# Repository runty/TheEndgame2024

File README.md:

# Endgame — RP2040-Zero Choc V2, nice!nano Choc V2 and nice!nano + Cirque

A 36-key [Endgame](https://github.com/OldMan6955/TheEndgame2024) repository with three builds. All three PCBs take Kailh Choc V2 (and Choc V1) hot-swap switches. Use the files for one build together; the PCBs, cases and firmware are not interchangeable.

| Build | Hardware and battery | PCB and matching case | Firmware and build notes |
| --- | --- | --- | --- |
| **RP2040-Zero Choc V2** (wired) | Waveshare RP2040-Zero, USB-C wired, original Endgame PCB outline and mounting | [JLCPCB Gerber ZIP](001%20PCB/GERBER/CHOC%20V1%20V2/TheEndgame2024_Choc_V1_V2_JLCPCB.zip) · [KiCad project](001%20PCB/KICAD/SILKSCREEN%20KICAD/) · [original case STEP](002%20CASE/TheENDGAME2024_CASE001.step) · Choc V2 plates: [3-D print](001%20PCB/PLATE%20CHOC%20V2/3D%20PRINT/), [1.2 mm FR-4/metal](001%20PCB/PLATE%20CHOC%20V2/) | [ZMK firmware](003%20FIRMWARE/zmk-endgame-rp2040-zero/) (sample keymap) · upstream [Vial UF2](003%20FIRMWARE/vial/endgame_vial.uf2) / [QMK config](003%20FIRMWARE/qmk-config-endgame/) · [Choc V1/V2 notes](docs/choc-v1-v2.md) |
| **nice!nano Choc V2** (wireless) | nice!nano v2, directly soldered 401730 LiPo (target ≤200 mAh), two axial resistors, WS2812B-V6 status LED | [223 × 96.11 mm Gerbers](001%20PCB/GERBER/NICE%20NANO%20WIRELESS/TheEndgame2024_NiceNano_223mm_THT_JLCPCB.zip) · [KiCad project](001%20PCB/KICAD/NICE%20NANO%20WIRELESS/) · [case (standard or clear LED logo) and tray](002%20CASE/NICE%20NANO%20WIRELESS/) | [ZMK firmware](003%20FIRMWARE/zmk-endgame-nice-nano/) · [build notes](docs/nice-nano-wireless.md) · [case notes](docs/nice-nano-case.md) |
| **nice!nano Choc V2 + Cirque** (wireless, touchpad) | nice!nano v2 plus a 40 mm Cirque TM040040 touchpad (curved overlay) between the thumbs; 401730 LiPo under the pad; JLCPCB-assembled SMD parts and FFC connector | [239 × 96.11 mm Gerbers + BOM/CPL](001%20PCB/GERBER/NICE%20NANO%20CIRQUE/) · [KiCad project](001%20PCB/KICAD/NICE%20NANO%20CIRQUE/) · [case, tray and pad carrier](002%20CASE/NICE%20NANO%20CIRQUE/) | [ZMK firmware](003%20FIRMWARE/zmk-endgame-nice-nano-cirque/) · [build notes](docs/nice-nano-cirque.md) |

**Case fit warning for nice!nano:** this PCB is 4 mm wider than the original and requires the matching **231 mm-wide nice!nano case** linked above. It does **not** fit the original Endgame case. Use the nice!nano-specific case files and plates.

The nice!nano version is **4 mm wider than the original PCB**. Each key half moves outward 2 mm, giving the inner keys more clearance from the controller while preserving the original outer borders. The controller, battery opening, and LED remain on the board's centreline. Its matching case retains the original height and sloped profile. The case has a relieved USB opening, and its inner thumb and top inner alpha opening edges match the original case; see the [thumb repair comparison](002%20CASE/NICE%20NANO%20WIRELESS/thumb-roof-repair-preview.png).

**Prototype status:** the RP2040-Zero Choc V2 board has been built, and all 36 keys work; keycap clearance on assembled hardware is unchecked. The nice!nano build has documented digital design, manufacturing-file, and CAD checks and has reached user assembly testing, with LED operation reported; the latest case repair, clear LED logo case, and printed thumb caps still need physical validation. Full system qualification and JLCPCB upload-preview verification remain incomplete. See the [2026-10-15 update](docs/updates-2026-10-15.md).

**nice!nano + Cirque (digital design, untested):** each half moves a further 8 mm outward (239 mm PCB, 247 mm case, same height) to fit the touchpad with its curved overlay and a 4 mm margin to the keycaps. The status LED moves to the right thumb gap. See the [nice!nano + Cirque notes](docs/nice-nano-cirque.md).

**RP2040-Zero Choc V2 PCB, top**

**nice!nano Choc V2 PCB, front**

**nice!nano Choc V2 + Cirque PCB, top**

## RP2040-Zero Choc V2 downloads

The original wired Endgame PCB with Choc V2 hot-swap support added (Choc V1 still fits). It keeps the original outline, mounting holes, controller position and 1.6 mm thickness, so it fits the original case.

| File | Download |
| --- | --- |
| JLCPCB manufacturing package | [Gerber ZIP](001%20PCB/GERBER/CHOC%20V1%20V2/TheEndgame2024_Choc_V1_V2_JLCPCB.zip) · [top](001%20PCB/GERBER/CHOC%20V1%20V2/top-preview.png) and [bottom](001%20PCB/GERBER/CHOC%20V1%20V2/bottom-preview.png) previews |
| Case | [Original case STEP](002%20CASE/TheENDGAME2024_CASE001.step) |
| Optional Choc V2 switch plates | [3-D print (recommended, test-fitted)](001%20PCB/PLATE%20CHOC%20V2/3D%20PRINT/) · [1.2 mm FR-4/metal](001%20PCB/PLATE%20CHOC%20V2/) · [notes](docs/choc-v1-v2.md#choc-v2-switch-plates) |
| Editable KiCad project | [SILKSCREEN KiCad project](001%20PCB/KICAD/SILKSCREEN%20KICAD/) (the released variant) |
| ZMK firmware (sample keymap) | [UF2](003%20FIRMWARE/zmk-endgame-rp2040-zero/firmware/endgame-rp2040-zero.uf2) · [settings reset UF2](003%20FIRMWARE/zmk-endgame-rp2040-zero/firmware/endgame-rp2040-zero-settings-reset.uf2) · [ZMK config and flashing notes](003%20FIRMWARE/zmk-endgame-rp2040-zero/) |
| Upstream QMK/Vial firmware | [Vial UF2](003%20FIRMWARE/vial/endgame_vial.uf2) · [QMK config](003%20FIRMWARE/qmk-config-endgame/); the key matrix is unchanged |
| Build details | [Compatibility, ordering, validation and prototype notes](docs/choc-v1-v2.md) |

Order **2 layers, 1.6 mm FR-4, 1 oz copper**, approximately **219 × 96.1 mm** (use the outline in the ZIP). Confirm the preview shows all 36 relief slots and 36 large centre holes. The older `SILKSCREEN GERBER` and `COPPER GERBER` folders are upstream Choc V1-only archives.

Prototype tips: the RP2040-Zero's 5V and GND pads are 0.84 mm apart, so check for a solder bridge before plugging in. If a whole column is dead, check continuity from its GP pin to the column socket tab; each column crosses to the front through a via beside its top-row switch.

## nice!nano downloads

Use the PCB, case, and firmware from this table together.

| File | Download |
| --- | --- |
| JLCPCB manufacturing package | [223 mm through-hole-resistor Gerber ZIP](001%20PCB/GERBER/NICE%20NANO%20WIRELESS/TheEndgame2024_NiceNano_223mm_THT_JLCPCB.zip) |
| Widened case (single filament) | [STL](002%20CASE/NICE%20NANO%20WIRELESS/TheENDGAME2024_NICE_NANO_CASE.stl) · [STEP](002%20CASE/NICE%20NANO%20WIRELESS/TheENDGAME2024_NICE_NANO_CASE.step) |
| Widened case with clear LED logo (two filaments) | [Bambu 3MF, two parts](002%20CASE/NICE%20NANO%20WIRELESS/LED%20LOGO/TheENDGAME2024_NICE_NANO_CASE_LED_LOGO.3mf) · body [STL](002%20CASE/NICE%20NANO%20WIRELESS/LED%20LOGO/TheENDGAME2024_NICE_NANO_CASE_LED_LOGO_BODY.stl)/[STEP](002%20CASE/NICE%20NANO%20WIRELESS/LED%20LOGO/TheENDGAME2024_NICE_NANO_CASE_LED_LOGO_BODY.step) · clear logo [STL](002%20CASE/NICE%20NANO%20WIRELESS/LED%20LOGO/TheENDGAME2024_NICE_NANO_CASE_LED_LOGO_CLEAR.stl)/[STEP](002%20CASE/NICE%20NANO%20WIRELESS/LED%20LOGO/TheENDGAME2024_NICE_NANO_CASE_LED_LOGO_CLEAR.step) · [preview](002%20CASE/NICE%20NANO%20WIRELESS/LED%20LOGO/led-logo-preview.png) · [notes](docs/nice-nano-case.md#optional-clear-led-logo-two-filament-print) |
| Removable battery tray with solder relief | [STL](002%20CASE/NICE%20NANO%20WIRELESS/TheENDGAME2024_NICE_NANO_BATTERY_TRAY.stl) · [STEP](002%20CASE/NICE%20NANO%20WIRELESS/TheENDGAME2024_NICE_NANO_BATTERY_TRAY.step) |
| Optional Choc V2 switch plates | [3-D print (recommended)](001%20PCB/PLATE%20CHOC%20V2/NICE%20NANO%20WIRELESS/3D%20PRINT/) · [1.2 mm FR-4/metal](001%20PCB/PLATE%20CHOC%20V2/NICE%20NANO%20WIRELESS/) · [notes](docs/nice-nano-case.md#choc-v2-switch-plates) |
| Editable KiCad project | [PCB](001%20PCB/KICAD/NICE%20NANO%20WIRELESS/TheEndgame2024_NiceNano.kicad_pcb) · [schematic](001%20PCB/KICAD/NICE%20NANO%20WIRELESS/TheEndgame2024_NiceNano.kicad_sch) · [project and local libraries](001%20PCB/KICAD/NICE%20NANO%20WIRELESS/) |
| nice!nano ZMK firmware (sample QWERTY keymap) | [UF2](003%20FIRMWARE/zmk-endgame-nice-nano/firmware/endgame-nice-nano-v2.uf2) · [ZMK source](003%20FIRMWARE/zmk-endgame-nice-nano/) |
| Build details | [Full BOM and assembly notes](docs/nice-nano-wireless.md) · [electrical](docs/nice-nano-electrical.md) · [case](docs/nice-nano-case.md) · [firmware](docs/nice-nano-firmware.md) |

## nice!nano JLCPCB order settings

| Setting | Value |
| --- | --- |
| Dimensions to enter | **223.00 × 96.11 mm** |
| Layers | **2** |
| Material | **FR-4** |
| Board thickness | **1.6 mm** |
| Copper weight | **1 oz** |

The measured Gerber outline is **223.000032 × 96.106067 mm**. Upload the ZIP intact: it contains the seven board layers, separate plated/non-plated drill files, and the Gerber job file. The **22 × 35 mm battery opening** is included as an internal routed contour. If dimensions need to be entered manually, use the rounded values above and check the board outline and battery opening in the preview.

## nice!nano fit and clearance

| Feature | Current design |
| --- | --- |
| Key field | 36 Choc V1/V2 hot-swap positions; each half moved outward 2 mm |
| Outer left/right 1U cap borders | **2.00 mm**, matching the original PCB with 17.5 × 16.5 mm caps |
| Keycap-to-controller clearance | **2.16 mm minimum** to the conservative 18 × 33 mm nice!nano envelope in CAD |
| Printed case width | **231 mm**, with the original overall height retained |
| USB opening | **15 mm wide**; lower side ledges removed; rear lip bevel adds 0.6 mm headroom while keeping at least 1.25 mm roof |
| Inner thumb and alpha edges | Original roof and opening edges restored beside the inner thumbs and top inner keys; existing switch plates retain 0.2 mm vertical clearance |
| Battery opening | **22 × 35 mm**, with 1 mm corner radii |
| Battery allowance checked | **18.5 × 33 × 5 mm** complete-pack envelope |

A centred **17 × 30 mm** battery leaves **2.5 mm on each side of the PCB opening**. The larger checked pack envelope leaves **1.75 mm per side and 1.0 mm at each end**, with **0.15 mm above the 5 mm-thick envelope** inside the case after the planned 0.2 mm support allowance. The actual wrapped battery and its lead exit still need measurement.

All 36 nominal **17.5 × 16.5 mm Chicago Steno 1U keycap envelopes** clear the case throughout a full-height CAD sweep, with a **0.70 mm minimum gap**, the same as the original case. Choc V2 requires **MX-stem** keycaps. The separate [thumb-cap package](006%20KEYCAPS/CHOC%20V2%20THUMBS/) includes larger-cap CAD checks; actual print tolerances and physical fit remain untested.

See the [measured layout and centreline](docs/validation/nice-nano-pcb/outer-key-symmetry.png), [keycap clearance comparison](docs/validation/nice-nano-case/cs-clearance.png), and [case preview](002%20CASE/NICE%20NANO%20WIRELESS/case-and-tray-preview.png).

The battery tray now includes an open center notch and corner relief for the underside resistor solder joints, following assembly feedback. Its screw mounts and the full planned battery support area are retained. See the [tray comparison](002%20CASE/NICE%20NANO%20WIRELESS/battery-tray-solder-clearance.png) and [case notes](docs/nice-nano-case.md).

## nice!nano electronics and assembly

- **nice!nano v2:** mount on short soldered posts, with USB facing the upper edge. Follow the [assembly-height limits](docs/nice-nano-case.md); standard sockets have not been qualified for this case.
- **Battery:** generic 401730 single-cell LiPo, target capacity ≤200 mAh. Solder its wires directly to **J1: pad 1 B+, pad 2 B−**. No JST connector is used. SW38 remains the physical battery disconnect.
- **Resistors:** R1 **330 Ω** and R2 **100 kΩ**, ordinary **¼ W axial through-hole** parts. Use nominal 6.3 × 2.5 mm bodies at **10.16 mm lead pitch**, mounted flat on the PCB's top side. The case accommodates bodies up to 6.5 × 2.5 mm; installation and lead-trimming limits are in the [BOM](docs/nice-nano-wireless.md#parts-and-assembly).
- **Status LED:** one **Worldsemi WS2812B-V6**, powered through nice!nano v2 switched VCC. With the standard case, a translucent case roof acts as the diffuser; the [clear LED logo case](docs/nice-nano-case.md#optional-clear-led-logo-two-filament-print) shows it through a transparent logo instead. The firmware adapts [zmk-rgbled-widget](https://github.com/caksoylar/zmk-rgbled-widget) for brief battery and Bluetooth/USB status flashes, then switches LED power off. See [LED meanings and limits](docs/nice-nano-firmware.md#status-indications).
- **Other parts:** C1 remains a **100 nF 0603 capacitor**, and the matrix retains **36 SOD-123 diodes and 36 Choc hot-swap sockets**. This is a hot-swap switch design; the original optional direct-solder switch pattern is not retained.

The [full parts list](docs/nice-nano-wireless.md#parts-and-assembly) includes controller posts, inserts, tray screws, feet, battery-fit assumptions, and charging requirements. Firmware is **ZMK for nice!nano v2**; the original wired QMK/Vial firmware does not apply to this revision.

## nice!nano verification

- **KiCad ERC, DRC, and schematic parity:** zero reported violations or unconnected items under the recorded rules. [ERC](docs/validation/nice-nano-schematic/erc.json) · [DRC](docs/validation/nice-nano-pcb/drc.json)
- **Independent Gerber parsing:** seven board layers, **226 plated and 148 non-plated holes/slots**, both contours closed, and drill registration checked against the PCB source. [Report](docs/validation/nice-nano-pcb/gerbers.json)
- **Mechanical checks:** mirrored key placement, preserved outer borders, centred electronics, valid single-solid STEP parts, watertight STL files, and component/keycap clearance checks. [Spacing](docs/validation/nice-nano-pcb/spacing.json) · [case](docs/validation/nice-nano-case/geometry.json)
- **Firmware:** pinned ZMK build and LED encoder host checks pass. The user reports working LED indications; hardware timing, charging, RF, and full keyboard operation remain unqualified. [Build and bring-up notes](docs/nice-nano-firmware.md)

The committed PCB is the authoritative manufacturing source. The scratch PCB generator is not a replacement for the finished routing. The [artifact manifest](docs/validation/nice-nano-artifacts.json) records source and output checksums.

## Choc V2 thumb keycaps

[Printable thumb caps and ordering notes](006%20KEYCAPS/CHOC%20V2%20THUMBS/) include **two separate connected 2 × 3 sets**: sculpted Chicago Steno thumbs and convex thumbs. Each contains **four long (1.5u) and two small (1u) caps**, with MX-style sockets for Choc V2 and removable connecting gates. These keycaps do not fit Choc V1 switches.

The cap envelopes clear the RP2040-Zero (original) and nice!nano cases in CAD. The meshes are verified locally; physical stem fit, print quality and JLC3DP acceptance remain untested. Upload the two files from the keycap folder's `upload` directory, quantity 1 each to try both profiles on one keyboard.

## Upstream documentation

This repository is based on the [original Endgame project](https://github.com/OldMan6955/TheEndgame2024). The original author's documentation is preserved below.

<details>
<summary>Original upstream README — wired Endgame, parts, credits, and photos</summary>

The following is the original project's documentation. Its controller, firmware, parts lists, manufacturing comments, and physical-test statements refer to the original Choc V1 wired design, not the RP2040-Zero Choc V2 or nice!nano Choc V2 builds above.

## Who the F... is Alice ##

Inspired by the legendary TGR Alice, the ENDGAME pays homage to a true classic. While it might not claim the top spot for ergonomics, it's design speaks for itself an iconic piece you’ll want to show off, even if it takes a bit of time for your fingers to adjust.

This low profile keyboard is built for high performance typing. Its slightly staggered layout works beautifully for both ergonomic beginners and experienced users. The unique bottomless top mount design makes it incredibly slim, lightweight, and perfect for those on the move.

## Everything You Need, All In One Place ##

Get the entire kit from KeebSupply, a trusted vendor with affordable international shipping. It’s your one stop shop for everything you need highly recommended! [Buy here](https://keeb.supply/products/endgame) 

For an excellent build guide, check out this fantastic resource from KeebSupply. I haven’t had the time to create my own guide (and honestly, I couldn’t top this one). Big thanks to @KeebSupply! [Build Guide and Supplies](https://docs.keeb.supply/endgame/) 

## PARTS LIST PCB ##

- 1x The Endgame PCB             [Gerber Files](https://github.com/OldMan6955/TheEndgame2024/tree/main/001%20PCB) 

There are now two versions of the PCB:
1.	COPPER Version:
In this version, all design elements are on the copper and mask layers. I used this version to create my prototypes. However, this version has longer loading times, and the Gerber files currently don’t work with JLCPCB. (I’d greatly appreciate any help with troubleshooting this issue.)
2.	SILKSCREEN Version:
This version is untested. All design elements have been moved to the silkscreen layer, making it much more performant on less powerful PCs. The Gerber files display correctly on JLCPCB but have not yet been tested.
Please always test the files yourself to rule out potential errors. Thank you!

- 36x Choc v1 Hotswap Sockets    [buy here](https://www.aliexpress.com/item/1005004916925259.html?) 
- 36x Diodes SOD123 / 1N4148W T4 [buy here](https://de.aliexpress.com/item/1005004309686841.html?) 
- 1x Waveshare RP2040 UGLY AF    [buy here](https://de.aliexpress.com/item/1005006354505058.html?) 

or get the better looking thingy, highly recommended

- | 01 | 0xCB Gemini             [buy here](https://keeb.supply/products/0xcb-gemini) |

## PARTS LIST FDM CASE ##

- 4x M3 6mm countersunk          [buy here](https://de.aliexpress.com/item/4001199728978.html) 
- 4x M3 5mm flathead             [buy here](https://de.aliexpress.com/item/1005005069968742.html) 

You can choose either countersunk or flathead screws both work well. Countersunk screws automatically align the PCB, while flathead screws allow you to manually align and adjust as needed.
The hole for the heat inserts is 4mm deep, and the PCB is 1.6mm thick, so 5mm screws are a perfect fit. Just double-check how the screw length is measured, as this can vary.

- 4x M3 D4.6mm L3mm Heatinsert   [buy here](https://de.aliexpress.com/item/4000232858343.html) 
- 12x M3 D6.6mm grommet black     [buy here](https://de.aliexpress.com/item/4000712868621.html) 

You’ll need 4 grommets if you’re aiming for a bit of flex or bounce, but you can use up to 12 depending on your preference. They work perfectly as feet and provide excellent grip on my desk. Alternatively, bumpons are a great option too.

## SWITCHES AND KEYCAPS ##

Switches

I highly recommend the Choc v1 Silent switches, such as [Nocturnal](https://keeb.supply/products/nocturnal-low-profile-switches) or [Twilights](https://keeb.supply/products/twilight-low-profile-switches). If you prefer heavier springs and a bit of tactile feedback but don’t need silence, [Sunset](https://keeb.supply/products/sunset-low-profile-switches) switches are an excellent choice. As for the rest of the Choc v1 lineup, I wouldn’t bother—they’re not worth considering.

Keycaps

My go-to choice is standard [MBK](https://keeb.supply/products/mbk-keycaps) keycaps, but personal preference always plays a role. For your setup, you’ll need:

- 30x 1U keycaps for the alpha keys (or 28x 1U and 2x 1U homing keycaps)
- 4x 1.5U and 2x 1U convex keycaps for the bottom row

Check with your local vendor, they’re in stock almost everywhere these days. A great way to test switches and keycaps is by attending meetups, there might be an active community near you.

## FIRMWARE - QMK AND VIAL ##

The firmware, expertly created by [dreipunkteinsvier](https://github.com/dreipunkteinsvier), is available for download: [Get it here](https://github.com/OldMan6955/TheEndgame2024/tree/main/003%20FIRMWARE) 
Huge thanks to him, I’d have been completely lost without his help!

## DISCLAIMER ##

This keyboard is an open-source project, and all files are provided free of charge for personal use. While these files have been tested and worked for me, they are provided without any guarantees or warranties of any kind.

By using these files, you agree to take full responsibility for verifying their suitability for your needs. Any orders, modifications, or reproductions made based on these files are done at your own risk. I am not liable for any issues, damages, or losses that may arise from the use of these files or the assembly of the keyboard.

Please ensure you carefully review all files and specifications before proceeding. Thank you for understanding!

## RANDOM PEOPLE I KNOW ##

After three years of development and collaboration with contributors from around the world, the ENDGAME is more than just a keyboard it’s the result of a shared journey, a community driven effort that reflects the passion and creativity of everyone involved.

- [Marco "Bob"](https://github.com/GroooveBob) - for answering all my dumb questions 24/7
- [dreipunkteinsvier](https://github.com/dreipunkteinsvier) - firmware and stupid github
- [bubbleology](https://github.com/bubbleology) - inspiration, CAD and emotional support
- [GEIST](https://github.com/GEIGEIGEIST) - can't remember what, but we talked about stuff back in the days RIP
- MY WIFE - for reasons
- and many more

To all who contributed thank you. Enjoy the journey, and have fun exploring what this keyboard can do!

## PICTURES ##

## ONLY FANS ##

While this project is free and open source, I truly appreciate your support. If you'd like to contribute, feel free to leave a tip via Ko-fi to help support future projects. Thank you!

## SHARE YOUR BUILDS ##

Do you love your ENDGAME? I’d love to see your builds! Join the Discord community to share pictures of your keyboards and chat with fellow enthusiasts.
Just a heads-up: I can’t help with technical issues or soldering nightmares because I’m still learning myself. So, please don’t ask me for help with that!

## FINAL WISDOM ##

    "The worst thing that can happen is someone calling me a keyboard designer."
    -OLDMAN6955

</details>

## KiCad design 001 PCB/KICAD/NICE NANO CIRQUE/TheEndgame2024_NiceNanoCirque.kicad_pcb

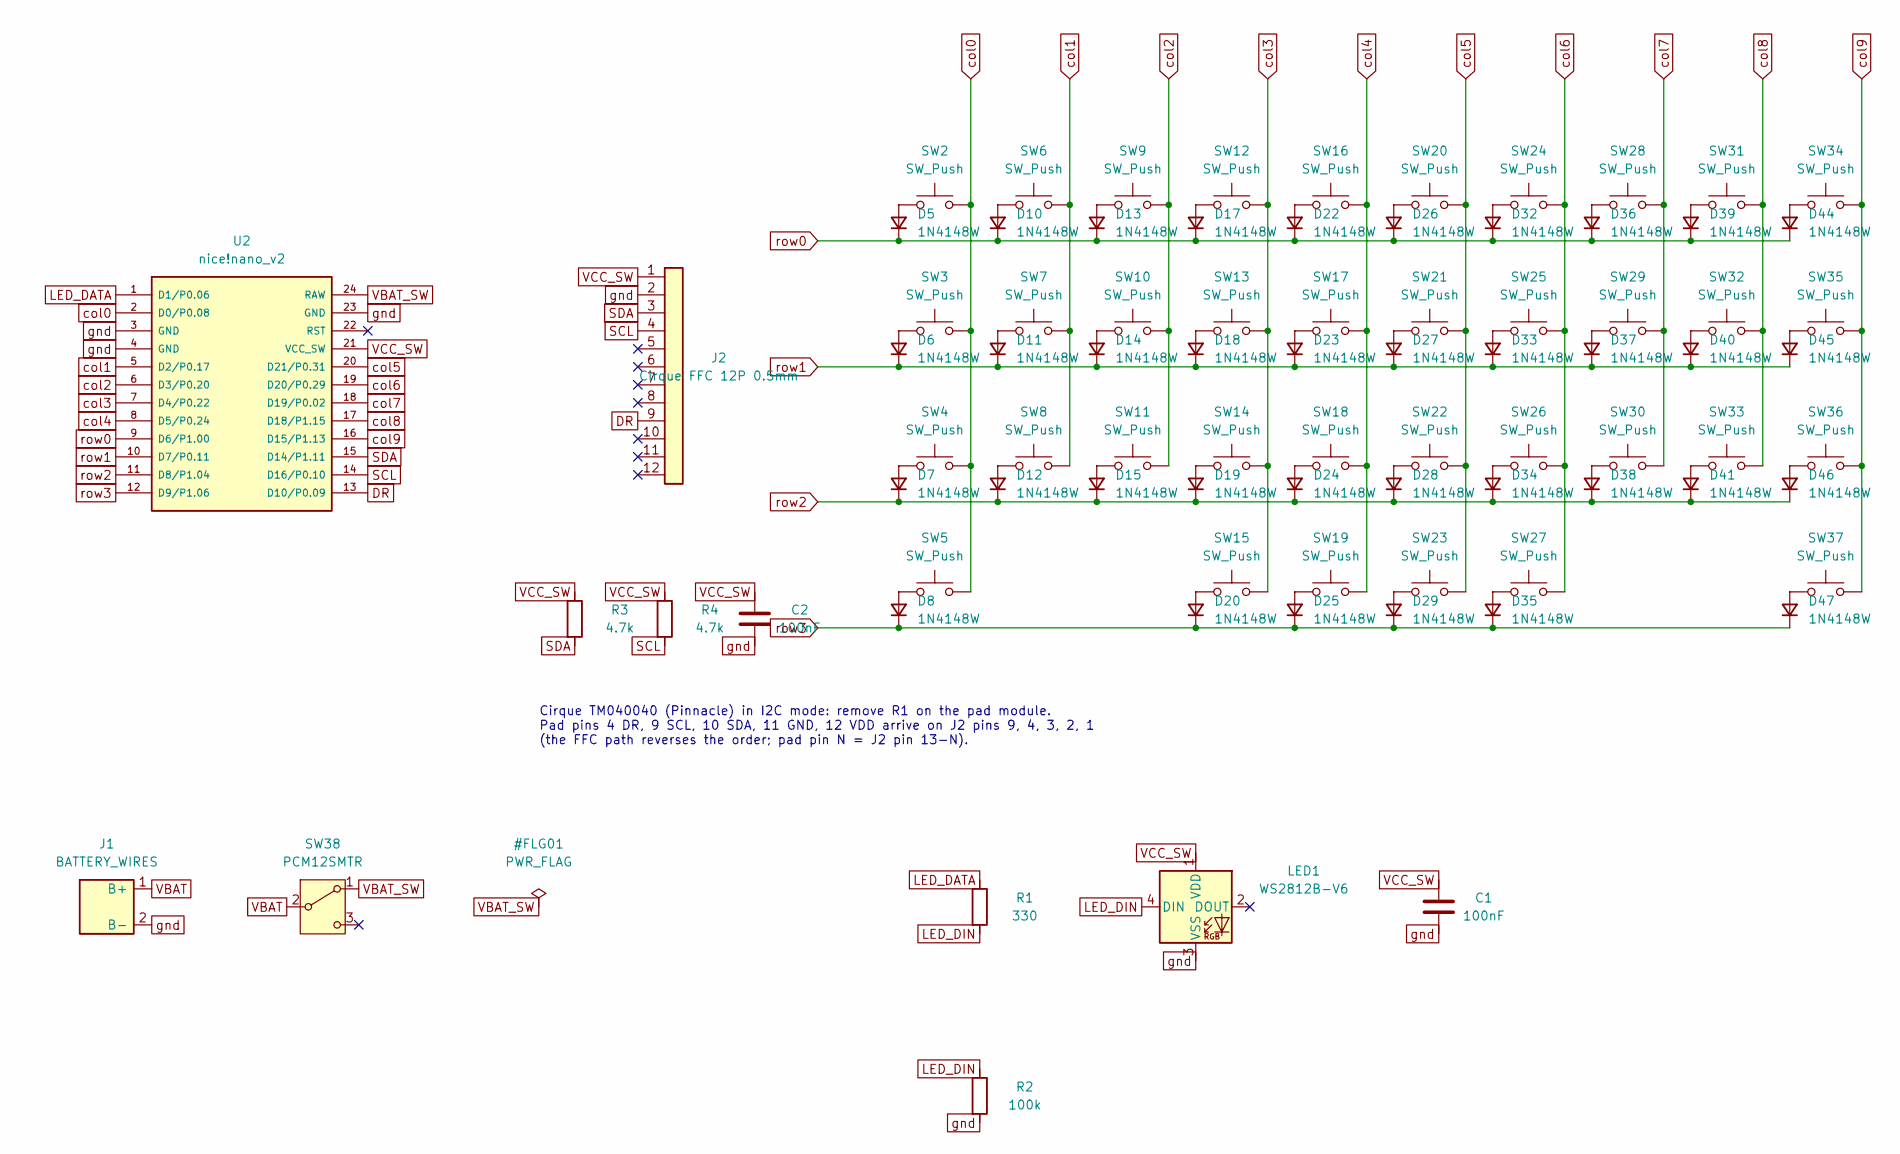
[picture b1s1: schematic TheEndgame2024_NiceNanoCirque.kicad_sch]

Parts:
C1, C2: 100nF; C_0603_1608Metric; LCSC C14663
D5, D6, D7, D8, D10, D11, D12, D13, D14, D15, D17, D18, D19, D20, D22, D23, D24, D25, D26, D27, D28, D29, D32, D33, D34, D35, D36, D37, D38, D39, D40, D41, D44, D45, D46, D47: 1N4148W; Diode_SOD123 filets triangle; LCSC C81598
J1: BATTERY_WIRES; Battery_Wire_Pads
J2: Cirque FFC 12P 0.5mm; JUSHUO_AFC01-S12FCA-00_1x12-1MP_P0.50mm_Horizontal; LCSC C262661
LED1: WS2812B-V6; WS2812B_V6_5050; LCSC C52917433
R1: 330; R_0603_1608Metric; LCSC C23138
R2: 100k; R_0603_1608Metric; LCSC C25803
R3, R4: 4.7k; R_0603_1608Metric; LCSC C23162
SW2, SW3, SW4, SW6, SW7, SW8, SW9, SW10, SW11, SW12, SW13, SW14, SW15, SW16, SW17, SW18, SW20, SW21, SW22, SW24, SW25, SW26, SW27, SW28, SW29, SW30, SW31, SW32, SW33, SW34, SW35, SW36: SW_Push; SW_choc_v1_v2_HS_1u
SW5, SW19, SW23, SW37: SW_Push; SW_choc_v1_v2_HS_1.5u
SW38: PCM12SMTR; PowerSwitch_PCM12
U2: nice!nano_v2; NiceNano_v2_PinPosts

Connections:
DR: J2.9, U2.13 (D10/P0.09)
LED_DATA: R1.1, U2.1 (D1/P0.06)
LED_DIN: LED1.4 (DIN), R1.2, R2.1
unnamed: D5.2 (A), SW2.1
unnamed: D6.2 (A), SW3.1
unnamed: D7.2 (A), SW4.1
unnamed: D8.2 (A), SW5.1
unnamed: D10.2 (A), SW6.1
unnamed: D11.2 (A), SW7.1
unnamed: D12.2 (A), SW8.1
unnamed: D13.2 (A), SW9.1
unnamed: D14.2 (A), SW10.1
unnamed: D15.2 (A), SW11.1
unnamed: D17.2 (A), SW12.1
unnamed: D18.2 (A), SW13.1
unnamed: D19.2 (A), SW14.1
unnamed: D20.2 (A), SW15.1
unnamed: D22.2 (A), SW16.1
unnamed: D23.2 (A), SW17.1
unnamed: D24.2 (A), SW18.1
unnamed: D25.2 (A), SW19.1
unnamed: D26.2 (A), SW20.1
unnamed: D27.2 (A), SW21.1
unnamed: D28.2 (A), SW22.1
unnamed: D29.2 (A), SW23.1
unnamed: D32.2 (A), SW24.1
unnamed: D33.2 (A), SW25.1
unnamed: D34.2 (A), SW26.1
unnamed: D35.2 (A), SW27.1
unnamed: D36.2 (A), SW28.1
unnamed: D37.2 (A), SW29.1
unnamed: D38.2 (A), SW30.1
unnamed: D39.2 (A), SW31.1
unnamed: D40.2 (A), SW32.1
unnamed: D41.2 (A), SW33.1
unnamed: D44.2 (A), SW34.1
unnamed: D45.2 (A), SW35.1
unnamed: D46.2 (A), SW36.1
unnamed: D47.2 (A), SW37.1
SCL: J2.4, R4.2, U2.14 (D16/P0.10)
SDA: J2.3, R3.2, U2.15 (D14/P1.11)
VBAT: J1.1 (B+), SW38.2 (B)
VBAT_SW: SW38.1 (A), U2.24 (RAW)
VCC_SW: C1.1, C2.1, J2.1, LED1.1 (VDD), R3.1, R4.1, U2.21 (VCC_SW)
col0: SW2.2, SW3.2, SW4.2, SW5.2, U2.2 (D0/P0.08)
col1: SW6.2, SW7.2, SW8.2, U2.5 (D2/P0.17)
col2: SW9.2, SW10.2, SW11.2, U2.6 (D3/P0.20)
col3: SW12.2, SW13.2, SW14.2, SW15.2, U2.7 (D4/P0.22)
col4: SW16.2, SW17.2, SW18.2, SW19.2, U2.8 (D5/P0.24)
col5: SW20.2, SW21.2, SW22.2, SW23.2, U2.20 (D21/P0.31)
col6: SW24.2, SW25.2, SW26.2, SW27.2, U2.19 (D20/P0.29)
col7: SW28.2, SW29.2, SW30.2, U2.18 (D19/P0.02)
col8: SW31.2, SW32.2, SW33.2, U2.17 (D18/P1.15)
col9: SW34.2, SW35.2, SW36.2, SW37.2, U2.16 (D15/P1.13)
gnd: C1.2, C2.2, J1.2 (B-), J2.2, LED1.3 (VSS), R2.2, U2.3 (GND), U2.4 (GND), U2.23 (GND)
row0: D5.1 (K), D10.1 (K), D13.1 (K), D17.1 (K), D22.1 (K), D26.1 (K), D32.1 (K), D36.1 (K), D39.1 (K), D44.1 (K), U2.9 (D6/P1.00)
row1: D6.1 (K), D11.1 (K), D14.1 (K), D18.1 (K), D23.1 (K), D27.1 (K), D33.1 (K), D37.1 (K), D40.1 (K), D45.1 (K), U2.10 (D7/P0.11)
row2: D7.1 (K), D12.1 (K), D15.1 (K), D19.1 (K), D24.1 (K), D28.1 (K), D34.1 (K), D38.1 (K), D41.1 (K), D46.1 (K), U2.11 (D8/P1.04)
row3: D8.1 (K), D20.1 (K), D25.1 (K), D29.1 (K), D35.1 (K), D47.1 (K), U2.12 (D9/P1.06)

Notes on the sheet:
Cirque TM040040 (Pinnacle) in I2C mode: remove R1 on the pad module. Pad pins 4 DR, 9 SCL, 10 SDA, 11 GND, 12 VDD arrive on J2 pins 9, 4, 3, 2, 1 (the FFC path reverses the order; pad pin N = J2 pin 13-N).

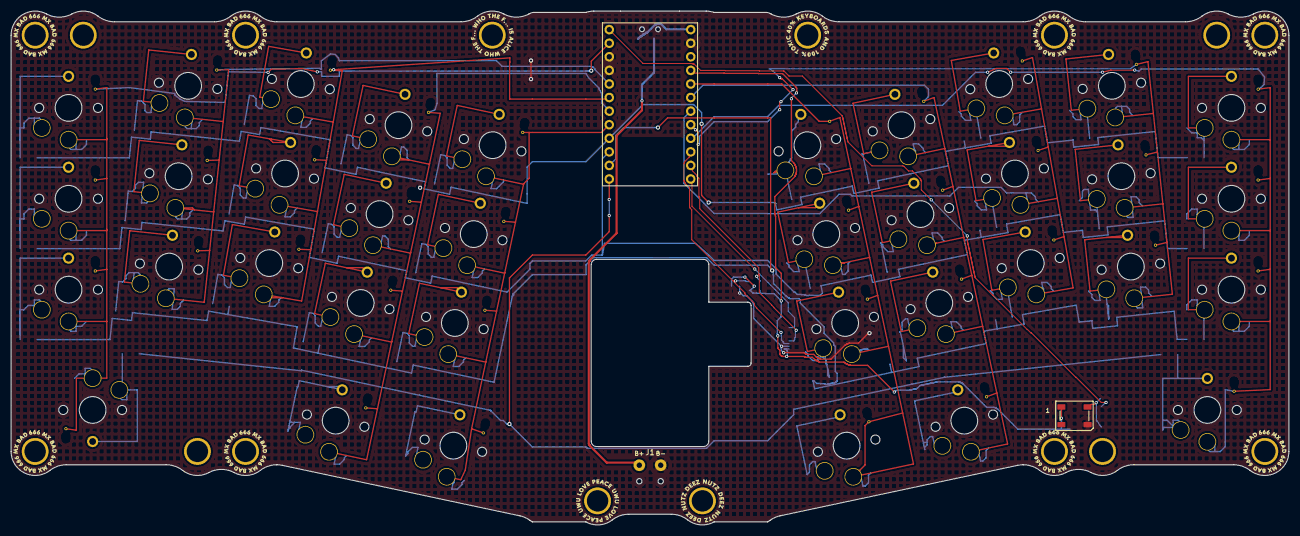
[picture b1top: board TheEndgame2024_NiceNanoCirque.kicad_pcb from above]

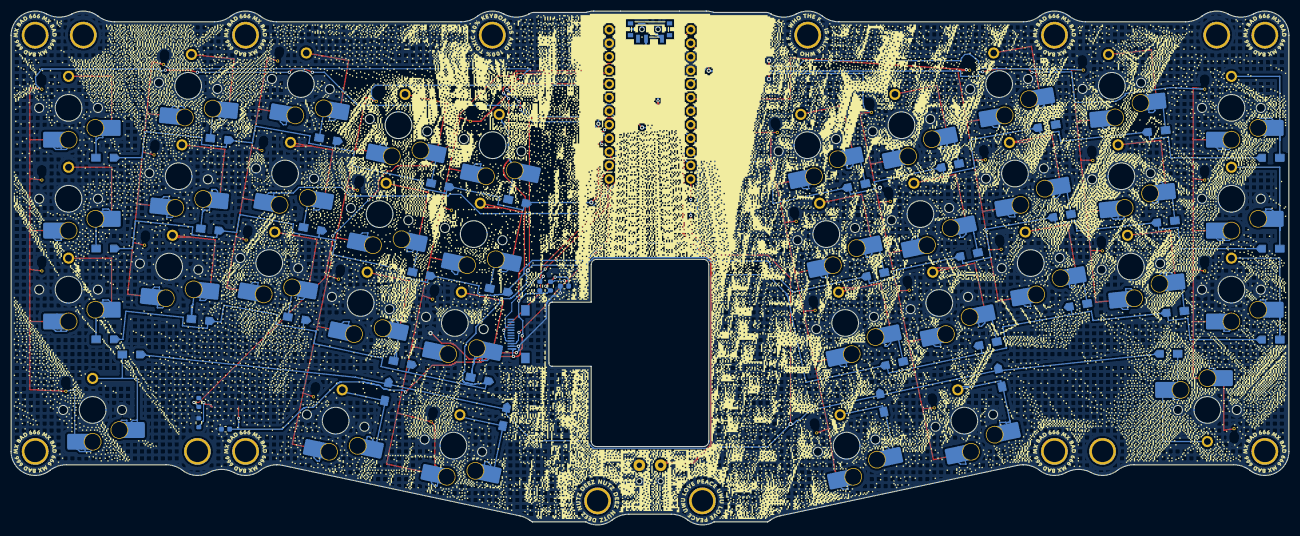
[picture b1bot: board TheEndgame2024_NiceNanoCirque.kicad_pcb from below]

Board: 2 copper layers, 239.0 x 96.1 mm, 83 parts (80 on the bottom side), 59 nets.

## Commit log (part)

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2026-06-12 Add Choc V2 clearance and JLCPCB gerbers
2026-06-12 Update README for JLCPCB gerbers
